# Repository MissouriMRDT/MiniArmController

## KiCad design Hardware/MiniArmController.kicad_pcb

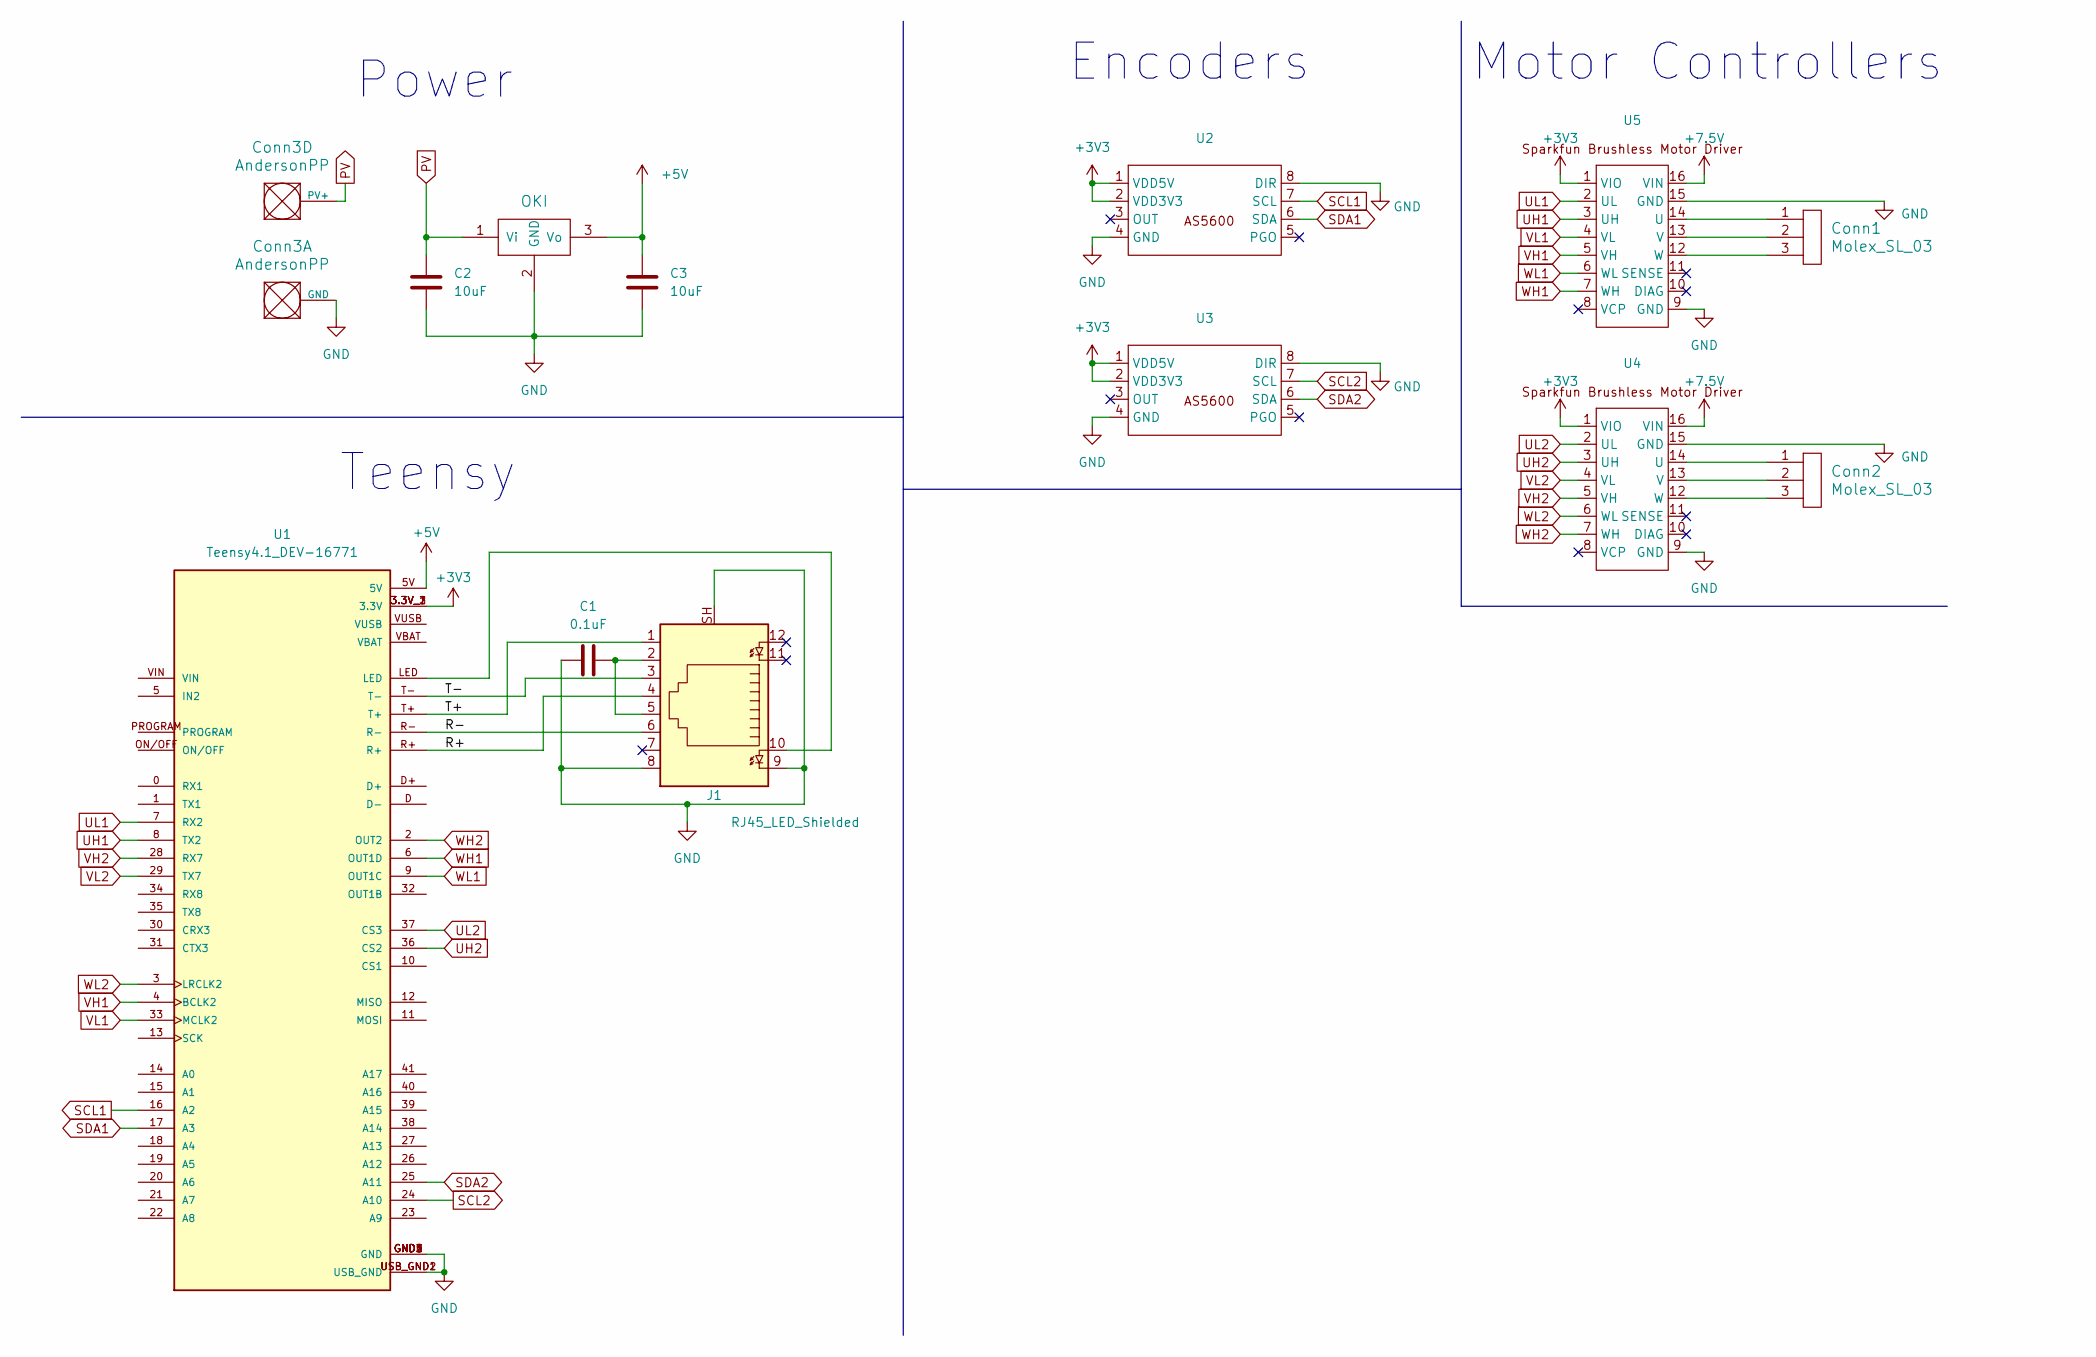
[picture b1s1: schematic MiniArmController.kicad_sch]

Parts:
C1: 0.1uF; C_0603_1608Metric_Pad1.08x0.95mm_HandSolder
C2: 10uF; C_1206_3216Metric_Pad1.33x1.80mm_HandSolder
C3: 10uF; C_0603_1608Metric_Pad1.08x0.95mm_HandSolder
Conn1, Conn2: Molex_SL_03; MOLEX_SL_03_Vertical
Conn3: AndersonPP; Square_Anderson_2_H_Side_By_Side_PV
J1: RJ45_LED_Shielded; RJ45_Teensy
U1: Teensy4.1_DEV-16771; Teensy_4_1; PARTREV 4.1
U2, U3: SOIC-8_3.9x4.9mm_P1.27mm
U4, U5: DIP-16_W12.7mm
U6: OKI; OKI_Horizontal

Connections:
+3V3: U1.3.3V_1 (3.3V), U1.3.3V_2 (3.3V), U1.3.3V_3 (3.3V), U2.1 (VDD5V), U2.2 (VDD3V3), U3.1 (VDD5V), U3.2 (VDD3V3), U4.1 (VIO), U5.1 (VIO)
+5V: C3.1, U1.5V, U6.3 (Vo)
+7.5V: U4.16 (VIN), U5.16 (VIN)
/R+: J1.4, U1.R+
/R-: J1.6, U1.R-
/T+: J1.1, U1.T+
/T-: J1.3, U1.T-
GND: C1.1, C2.2, C3.2, Conn3.1 (GND), J1.8, J1.9, J1.SH, U1.GND1 (GND), U1.GND2 (GND), U1.GND3 (GND), U1.GND4 (GND), U1.GND5 (GND), U1.USB_GND1 (USB_GND), U1.USB_GND2 (USB_GND), U2.4 (GND), U2.8 (DIR), U3.4 (GND), U3.8 (DIR), U4.9 (GND), U4.15 (GND), U5.9 (GND), U5.15 (GND), U6.2 (GND)
unnamed: C1.2, J1.2, J1.5
unnamed: J1.10, U1.LED
unnamed: Conn2.1, U4.14 (U)
unnamed: Conn2.2, U4.13 (V)
unnamed: Conn2.3, U4.12 (W)
unnamed: Conn1.1, U5.14 (U)
unnamed: Conn1.2, U5.13 (V)
unnamed: Conn1.3, U5.12 (W)
PV: C2.1, Conn3.4 (PV+), U6.1 (Vi)
SCL1: U1.16 (A2), U2.7 (SCL)
SCL2: U1.24 (A10), U3.7 (SCL)
SDA1: U1.17 (A3), U2.6 (SDA)
SDA2: U1.25 (A11), U3.6 (SDA)
UH1: U1.8 (TX2), U5.3 (UH)
UH2: U1.36 (CS2), U4.3 (UH)
UL1: U1.7 (RX2), U5.2 (UL)
UL2: U1.37 (CS3), U4.2 (UL)
VH1: U1.4 (BCLK2), U5.5 (VH)
VH2: U1.28 (RX7), U4.5 (VH)
VL1: U1.33 (MCLK2), U5.4 (VL)
VL2: U1.29 (TX7), U4.4 (VL)
WH1: U1.6 (OUT1D), U5.7 (WH)
WH2: U1.2 (OUT2), U4.7 (WH)
WL1: U1.9 (OUT1C), U5.6 (WL)
WL2: U1.3 (LRCLK2), U4.6 (WL)

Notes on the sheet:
Power
Encoders
Motor Controllers
Teensy

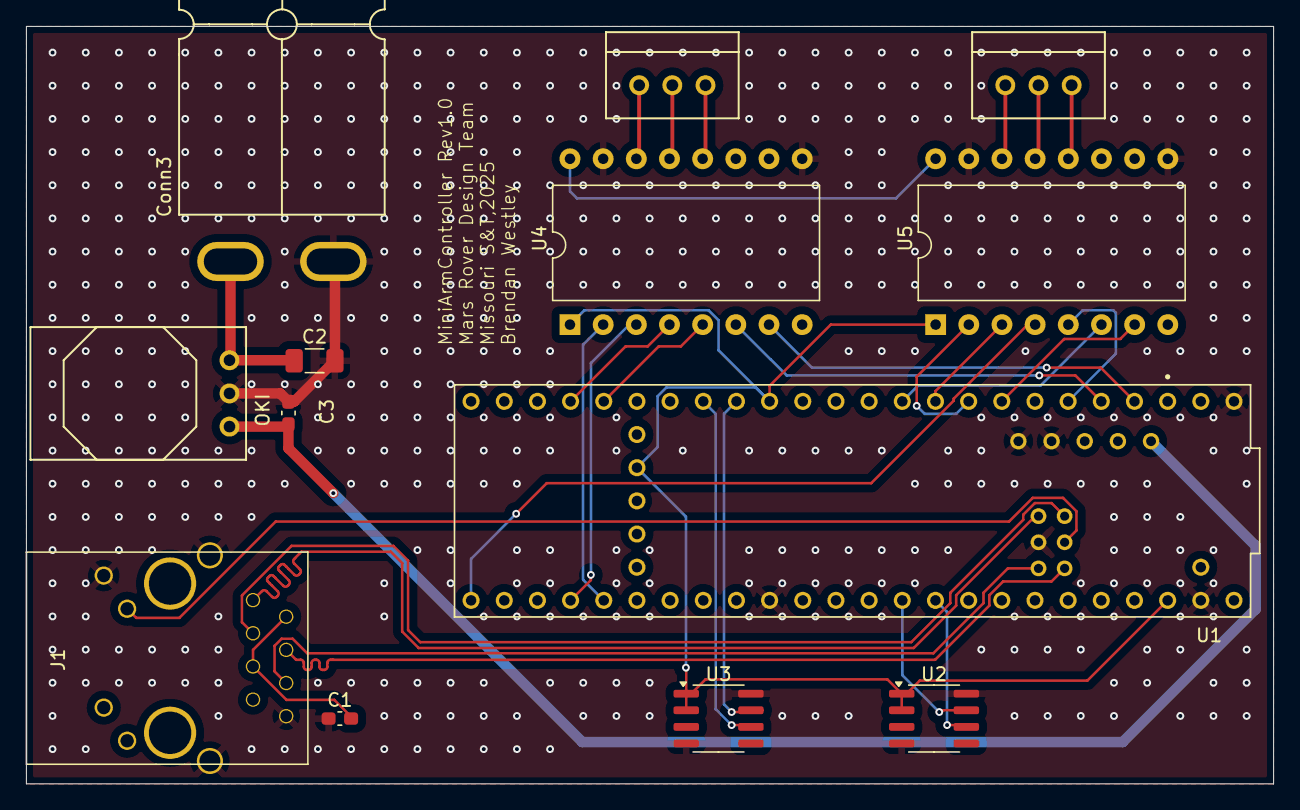
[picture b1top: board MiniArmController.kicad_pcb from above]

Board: 2 copper layers, 95.5 x 58.0 mm, 13 parts (0 on the bottom side), 33 nets.

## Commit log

2024-10-02 Test AS5600
2024-10-17 Add two encoders as a mouse
2024-10-18 Add two 3215BLCD motors
2024-11-15 Superseded board changes
2024-11-18 Superseded changes
